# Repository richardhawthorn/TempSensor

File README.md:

### Description

PCB and Arduino code for a basic temperature sensor

### Features

- 4 character 7-segment LED display
- ATMEGA328P with Arduino boot-loader
- 5V operation @ 16Mhz
- DS18B20 temperature sensor
- 1x button to select unit
- Mini USB power connector
- FTDI programming port
- ICSP port

### License

This work is licensed under a Creative Commons Attribution-ShareAlike 4.0 International License.

<br />
Designed by <a xmlns:cc="http://creativecommons.org/ns#" href="http://www.richardhawthorn.com" property="cc:attributionName" rel="cc:attributionURL" target="_blank">Richard Hawthorn</a><br />
<a rel="license" href="http://creativecommons.org/licenses/by-sa/4.0/" target="_blank">View License</a>

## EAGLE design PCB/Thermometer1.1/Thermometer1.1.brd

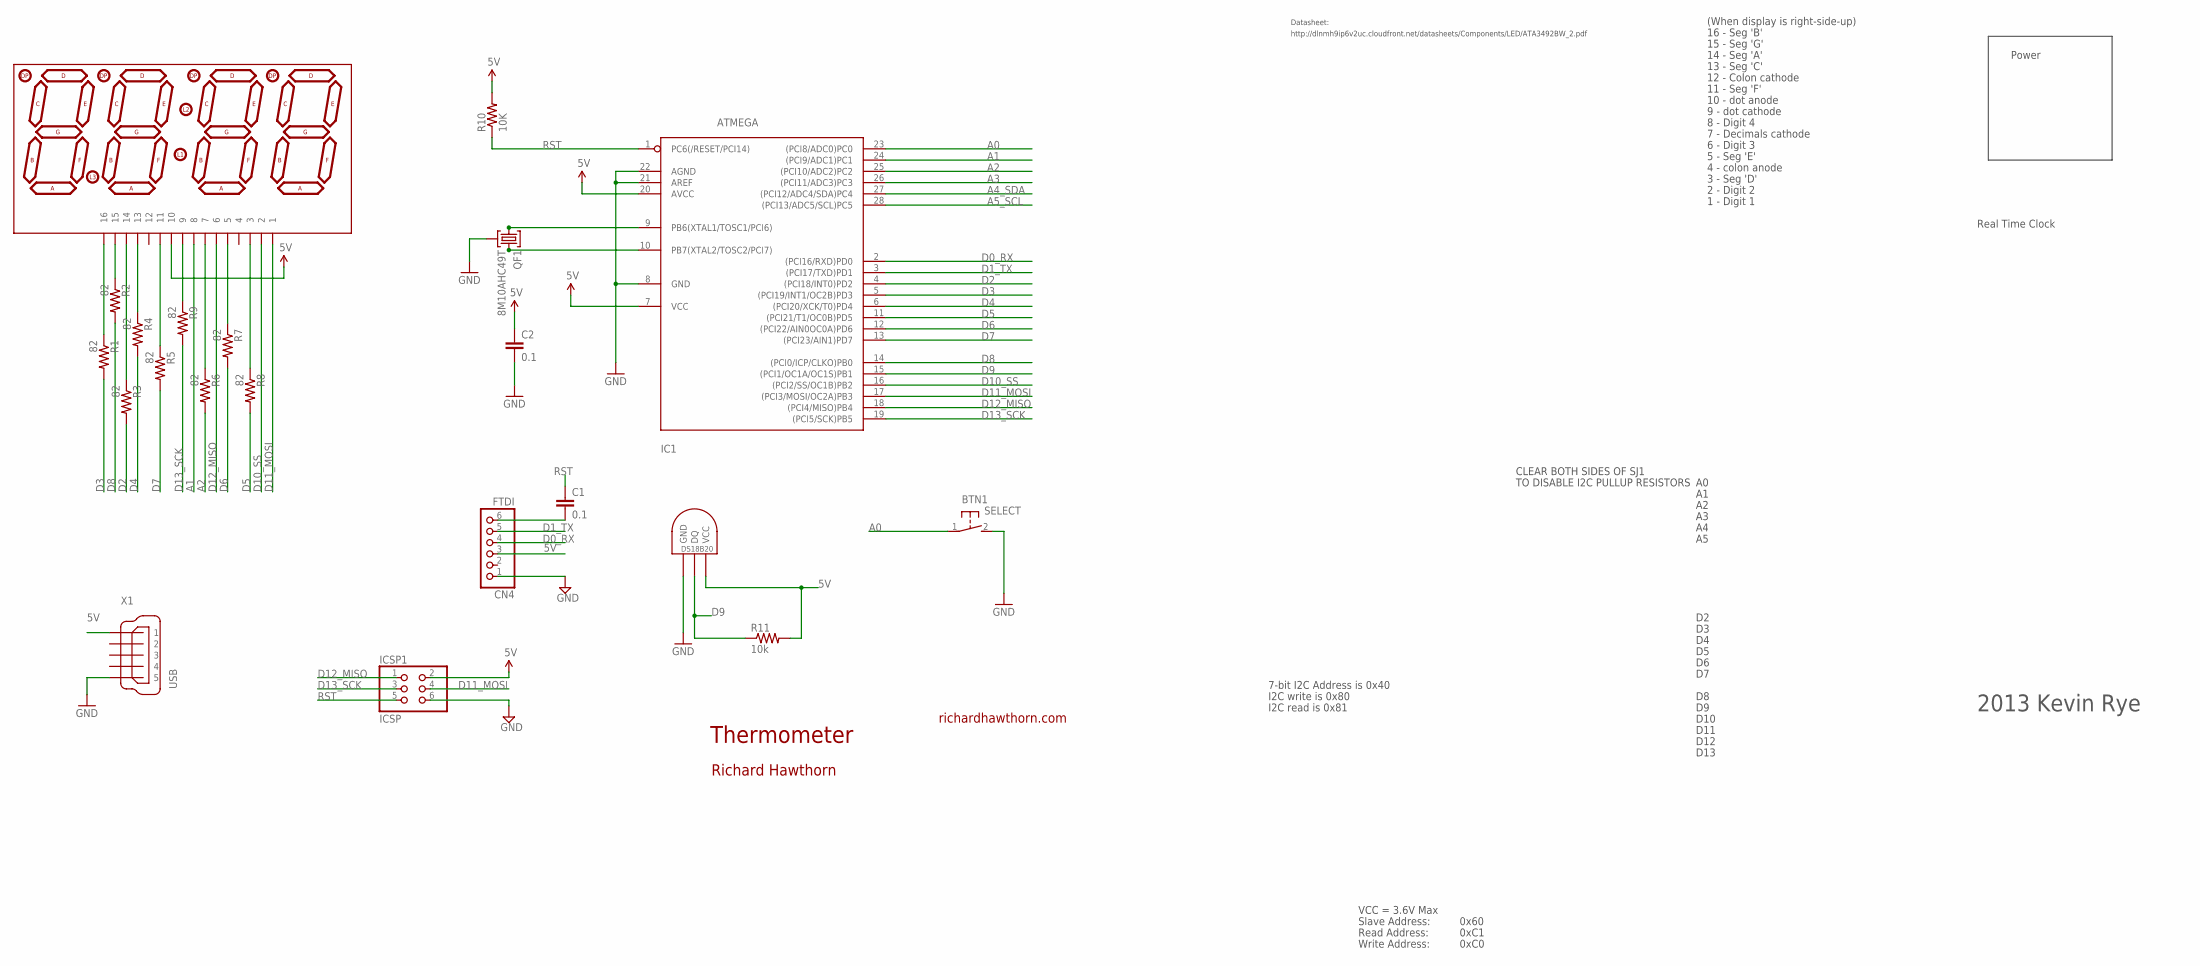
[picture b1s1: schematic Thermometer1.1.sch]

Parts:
BTN1: SELECT; DTS-3
C1, C2: 0.1; CAP-PTH-SMALL2
CN4: FTDI; 1X06
IC1: ATMEGA; DIL28-3-ROUND
ICSP1: ICSP; 2X03
LED1: 7SEG-4DIGIT; SPARKFUN_7-SEGMENT-4DIGIT
QF1: 8M10AHC49T; HC49U
R1, R2, R3, R4, R5, R6, R7, R8, R9: 82; 0204/7
R10: 10K; 0204/7
R11: 10k; 0204/7
U$1: DS1820TO92; DS1820
X1: USB; 32005-601

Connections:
5V: C2.1, CN4.3, IC1.7 (VCC), IC1.20 (AVCC), ICSP1.2, LED1.10, R10.2, R11.2, U$1.VDD (VCC), X1.1
A0: BTN1.1, IC1.23 ((PCI8/ADC0)PC0)
A1: IC1.24 ((PCI9/ADC1)PC1), R9.2
A2: IC1.25 ((PCI10/ADC2)PC2), R6.2
A3: IC1.26 ((PCI11/ADC3)PC3)
A4_SDA: IC1.27 ((PCI12/ADC4/SDA)PC4)
A5_SCL: IC1.28 ((PCI13/ADC5/SCL)PC5)
D0_RX: CN4.4, IC1.2 ((PCI16/RXD)PD0)
D1_TX: CN4.5, IC1.3 ((PCI17/TXD)PD1)
D2: IC1.4 ((PCI18/INT0)PD2), R3.2
D3: IC1.5 ((PCI19/INT1/OC2B)PD3), R1.2
D4: IC1.6 ((PCI20/XCK/T0)PD4), R4.2
D5: IC1.11 ((PCI21/T1/OC0B)PD5), R8.2
D6: IC1.12 ((PCI22/AIN0OC0A)PD6), R7.2
D7: IC1.13 ((PCI23/AIN1)PD7), R5.2
D8: IC1.14 ((PCI0/ICP/CLKO)PB0), R2.2
D9: IC1.15 ((PCI1/OC1A/OC1S)PB1), R11.1, U$1.DQ
D10_SS: IC1.16 ((PCI2/SS/OC1B)PB2), LED1.1
D11_MOSI: IC1.17 ((PCI3/MOSI/OC2A)PB3), ICSP1.4, LED1.2
D12_MISO: IC1.18 ((PCI4/MISO)PB4), ICSP1.1, LED1.6
D13_SCK: IC1.19 ((PCI5/SCK)PB5), ICSP1.3, LED1.8
GND: BTN1.2, C2.2, CN4.1, IC1.8 (GND), IC1.21 (AREF), IC1.22 (AGND), ICSP1.6, QF1.2, U$1.GND, X1.5
unnamed: LED1.16, R1.1
unnamed: LED1.15, R2.1
unnamed: LED1.9, R9.1
unnamed: LED1.7, R6.1
unnamed: IC1.9 (PB6(XTAL1/TOSC1/PCI6)), QF1.1
unnamed: C1.2, CN4.6
unnamed: LED1.13, R4.1
unnamed: LED1.14, R3.1
unnamed: LED1.11, R5.1
unnamed: IC1.10 (PB7(XTAL2/TOSC2/PCI7)), QF1.3
unnamed: LED1.5, R7.1
unnamed: LED1.3, R8.1
RST: C1.1, IC1.1 (PC6(/RESET/PCI14)), ICSP1.5, R10.1

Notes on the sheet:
Thermometer
richardhawthorn.com
Richard Hawthorn
CLEAR BOTH SIDES OF SJ1
TO DISABLE I2C PULLUP RESISTORS
7-bit I2C Address is 0x40
I2C write is 0x80
I2C read is 0x81
VCC = 3.6V Max
Read Address:
Write Address:
Slave Address:
0x60
0xC1
0xC0
14 - Seg 'A'
13 - Seg 'C'
12 - Colon cathode
11 - Seg 'F'
10 - dot anode
9 - dot cathode
8 - Digit 4
7 - Decimals cathode
6 - Digit 3
5 - Seg 'E'
4 - colon anode
3 - Seg 'D'
2 - Digit 2
Real Time Clock
1 - Digit 1
15 - Seg 'G'
16 - Seg 'B'
D10
D11
D12
D13
http://dlnmh9ip6v2uc.cloudfront.net/datasheets/Components/LED/ATA3492BW_2.pdf
Datasheet:
Power
(When display is right-side-up)

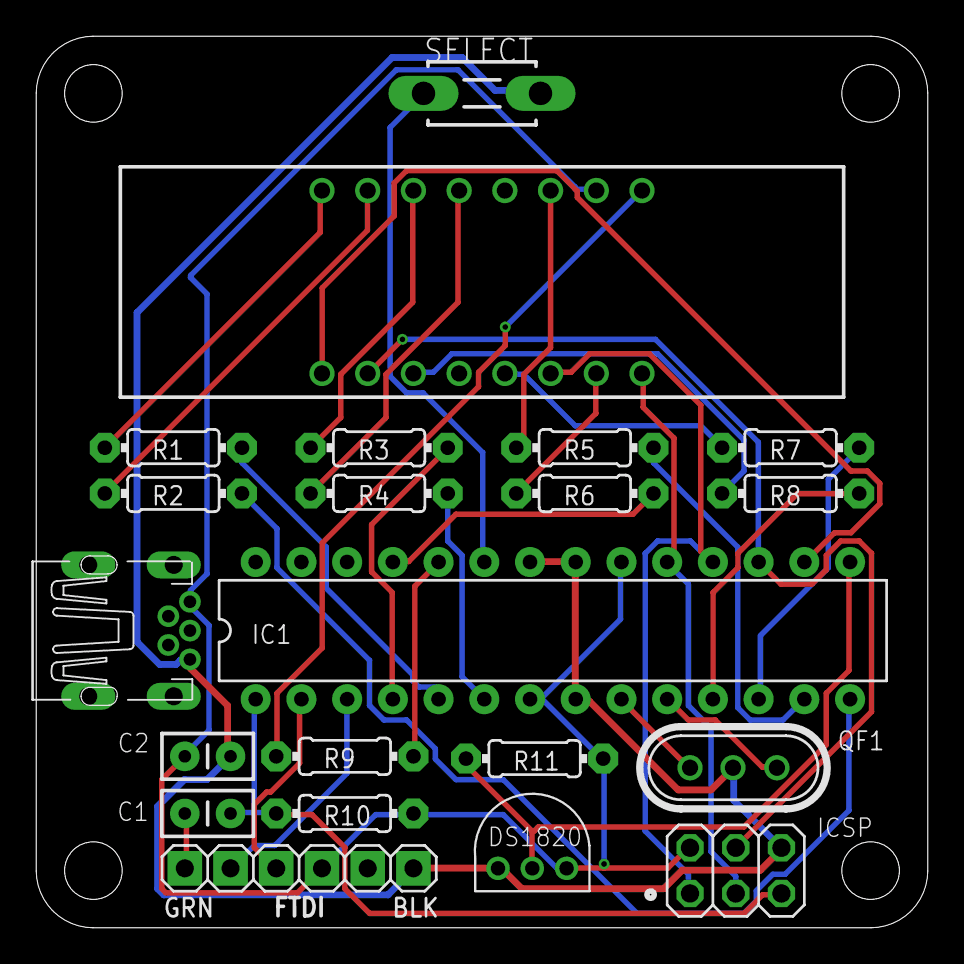
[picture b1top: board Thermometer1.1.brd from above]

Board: 2 copper layers, 49.5 x 49.5 mm, 22 parts (1 on the bottom side), 32 nets.

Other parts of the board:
U$3: OSHW-LOGO-S

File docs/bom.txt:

### Parts list

Qty  Value       Description          Parts 
           
2    0.1         Capacitor            C1, C2                                        
1    10K         Resistor             R10, R11                                              
1    7SEG        7 Segment LED        LED1           
9    82r         Resistor             R1, R2, R3, R4, R5, R6, R7, R8, R9     
1    8M10AHC49T  Crystal              QF1          
1    ATMEGA328P  Microcontroller      IC1                                        
1    DS1820      Temp Sensor          U$1                             
1    FTDI        6 Pin Header         CN4                                                                
1    SELECT      Button               BTN1                                             
1    USB         USB connector 	      X1    

### Additional Hardware

1 x IC Socket  
1 x PCB  
1 x Front Plate  
4 x Pillars  
8 x Screws

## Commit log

2016-01-26 adding pcb for v1.1
2016-01-26 adding images
2016-01-26 adding bom
2016-01-26 adding arduino code

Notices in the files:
parts and their libraries:
SparkFun-Aesthetics: Licensing: CC v3.0 Share-Alike You are welcome to use this library for commercial purposes.
